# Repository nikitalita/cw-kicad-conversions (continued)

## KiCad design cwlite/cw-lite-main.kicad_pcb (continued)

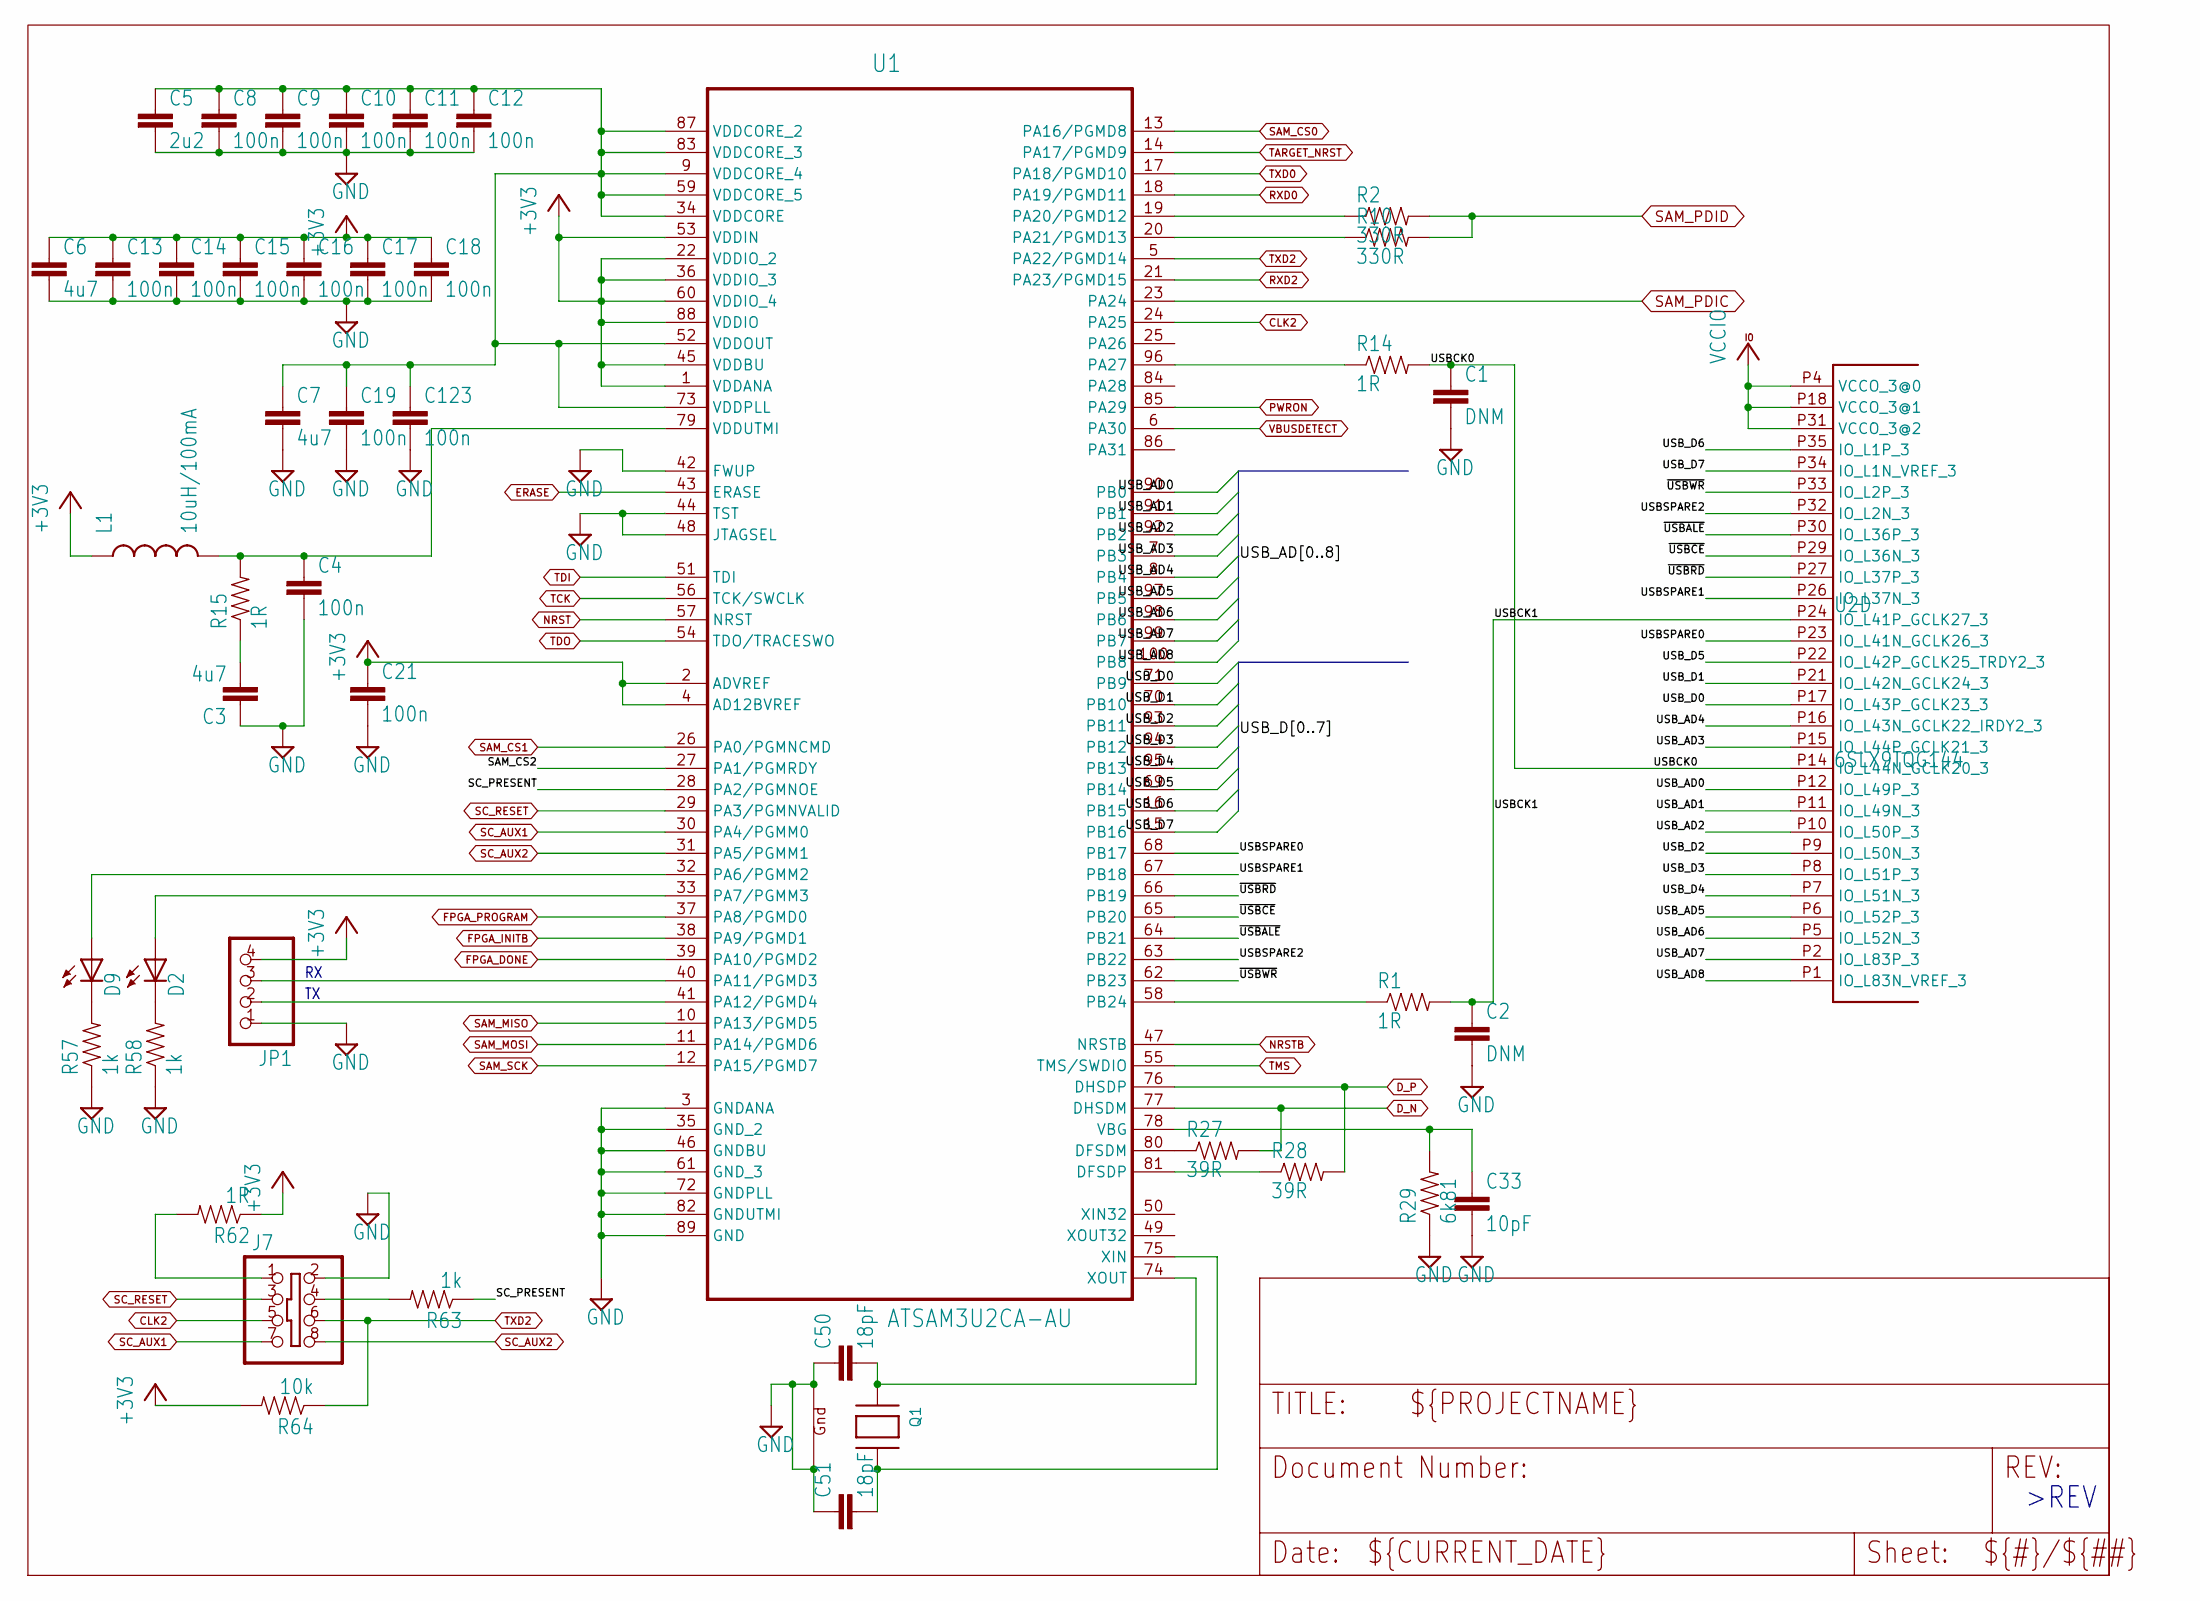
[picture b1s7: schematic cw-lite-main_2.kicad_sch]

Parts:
C1, C2: DNM; 0402C
C3, C6, C7: 4u7; 0603C
C4, C8, C9, C10, C11, C12, C13, C14, C15, C16, C17, C18, C19, C21, C123: 100n; 0402C
C5: 2u2; 0603C
C33: 10pF; 0603C
C50, C51: 18pF; 0402C
D2, D9: LED0603; LED-0603
J7: SHROUD_2X4EDGE; PINSHRD_EDGE_2X04.PAC
JP1: PINHD-1X4; 1X04
L1: 10uH/100mA; 0603
Q1: XTAL-4ABM8G; NX3225; MPN ABM8G-12.000MHZ-4Y-T3
R1, R14: 1R; 0402R
R2, R10: 330R; 0402R
R15, R62: 1R; 0603R
R27, R28: 39R; 0603R
R29: 6k81; 0402R
R57, R58, R63: 1k; 0603R
R64: 10k; 0603R
U1: ATSAM3U2CA-AU; QFP50P1600X1600X160-100N
U2: 6SLX9TQG144; TQ144; MPN XC6SLX9-3TQG144C

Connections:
+3V3: C6.1, C13.1, C14.1, C15.1, C16.1, C17.1, C18.1, C21.1, JP1.4, L1.1, R62.1, R64.2, U1.1 (VDDANA), U1.2 (ADVREF), U1.4 (AD12BVREF), U1.22 (VDDIO_2), U1.36 (VDDIO_3), U1.45 (VDDBU), U1.53 (VDDIN), U1.60 (VDDIO_4), U1.88 (VDDIO); also elsewhere on the board
/cw-lite-main_2/SAM_CS2: U1.27 (PA1/PGMRDY)
/cw-lite-main_2/SC_PRESENT: R63.1, U1.28 (PA2/PGMNOE)
/cw-lite-main_2/USBCK0: C1.1, R14.2, U2.P14 (IO_L44N_GCLK20_3)
/cw-lite-main_2/USBCK1: C2.1, R1.2, U2.P24 (IO_L41P_GCLK27_3)
/cw-lite-main_2/USBSPARE0: U1.68 (PB17), U2.P23 (IO_L41N_GCLK26_3)
/cw-lite-main_2/USBSPARE1: U1.67 (PB18), U2.P26 (IO_L37N_3)
/cw-lite-main_2/USBSPARE2: U1.63 (PB22), U2.P32 (IO_L2N_3)
/cw-lite-main_2/USB_AD0: U1.90 (PB0), U2.P12 (IO_L49P_3)
/cw-lite-main_2/USB_AD1: U1.91 (PB1), U2.P11 (IO_L49N_3)
/cw-lite-main_2/USB_AD2: U1.92 (PB2), U2.P10 (IO_L50P_3)
/cw-lite-main_2/USB_AD3: U1.7 (PB3), U2.P15 (IO_L44P_GCLK21_3)
/cw-lite-main_2/USB_AD4: U1.8 (PB4), U2.P16 (IO_L43N_GCLK22_IRDY2_3)
/cw-lite-main_2/USB_AD5: U1.97 (PB5), U2.P6 (IO_L52P_3)
/cw-lite-main_2/USB_AD6: U1.98 (PB6), U2.P5 (IO_L52N_3)
/cw-lite-main_2/USB_AD7: U1.99 (PB7), U2.P2 (IO_L83P_3)
/cw-lite-main_2/USB_AD8: U1.100 (PB8), U2.P1 (IO_L83N_VREF_3)
/cw-lite-main_2/USB_D0: U1.71 (PB9), U2.P17 (IO_L43P_GCLK23_3)
/cw-lite-main_2/USB_D1: U1.70 (PB10), U2.P21 (IO_L42N_GCLK24_3)
/cw-lite-main_2/USB_D2: U1.93 (PB11), U2.P9 (IO_L50N_3)
/cw-lite-main_2/USB_D3: U1.94 (PB12), U2.P8 (IO_L51P_3)
/cw-lite-main_2/USB_D4: U1.95 (PB13), U2.P7 (IO_L51N_3)
/cw-lite-main_2/USB_D5: U1.69 (PB14), U2.P22 (IO_L42P_GCLK25_TRDY2_3)
/cw-lite-main_2/USB_D6: U1.16 (PB15), U2.P35 (IO_L1P_3)
/cw-lite-main_2/USB_D7: U1.15 (PB16), U2.P34 (IO_L1N_VREF_3)
/cw-lite-main_2/~USBALE: U1.64 (PB21), U2.P30 (IO_L36P_3)
/cw-lite-main_2/~USBCE: U1.65 (PB20), U2.P29 (IO_L36N_3)
/cw-lite-main_2/~USBRD: U1.66 (PB19), U2.P27 (IO_L37P_3)
/cw-lite-main_2/~USBWR: U1.62 (PB23), U2.P33 (IO_L2P_3)
CLK2: J7.5, U1.24 (PA25); also elsewhere on the board
D_N: R27.2, U1.77 (DHSDM); also elsewhere on the board
D_P: R28.2, U1.76 (DHSDP); also elsewhere on the board
ERASE: U1.43 (ERASE); also elsewhere on the board
FPGA_DONE: U1.39 (PA10/PGMD2); also elsewhere on the board
FPGA_INITB: U1.38 (PA9/PGMD1); also elsewhere on the board
FPGA_PROGRAM: U1.37 (PA8/PGMD0); also elsewhere on the board
GND: C1.2, C2.2, C3.1, C4.2, C5.2, C6.2, C7.2, C8.2, C9.2, C10.2, C11.2, C12.2, C13.2, C14.2, C15.2, C16.2, C17.2, C18.2, C19.2, C21.2, C33.2, C50.1, C51.1, C123.2, J7.2, JP1.1, Q1.2 (G1), Q1.4 (G2), R29.1, R57.1, R58.1, U1.3 (GNDANA), U1.35 (GND_2), U1.42 (FWUP), U1.44 (TST), U1.46 (GNDBU), U1.48 (JTAGSEL), U1.61 (GND_3), U1.72 (GNDPLL), U1.82 (GNDUTMI), U1.89 (GND); also elsewhere on the board
NRST: U1.57 (NRST); also elsewhere on the board
NRSTB: U1.47 (NRSTB); also elsewhere on the board
unnamed: C3.2, R15.1
unnamed: D2.C, R58.2
unnamed: D9.C, R57.2
unnamed: J7.1, R62.2
unnamed: J7.4, R63.2
unnamed: C50.2, Q1.1 (X1), U1.74 (XOUT)
unnamed: C51.2, Q1.3 (X2), U1.75 (XIN)
unnamed: R27.1, U1.80 (DFSDM)
unnamed: R28.1, U1.81 (DFSDP)
unnamed: D9.A, U1.32 (PA6/PGMM2)
unnamed: D2.A, U1.33 (PA7/PGMM3)
unnamed: JP1.3, U1.40 (PA11/PGMD3)
unnamed: JP1.2, U1.41 (PA12/PGMD4)
unnamed: R2.1, U1.19 (PA20/PGMD12)
unnamed: R10.1, U1.20 (PA21/PGMD13)
unnamed: R14.1, U1.96 (PA27)
unnamed: R1.1, U1.58 (PB24)
unnamed: C33.1, R29.2, U1.78 (VBG)
unnamed: C5.1, C7.1, C8.1, C9.1, C10.1, C11.1, C12.1, C19.1, C123.1, U1.9 (VDDCORE_4), U1.34 (VDDCORE), U1.52 (VDDOUT), U1.59 (VDDCORE_5), U1.73 (VDDPLL), U1.83 (VDDCORE_3), U1.87 (VDDCORE_2)
unnamed: C4.1, L1.2, R15.2, U1.79 (VDDUTMI)
PWRON: U1.85 (PA29); also elsewhere on the board
RXD0: U1.18 (PA19/PGMD11); also elsewhere on the board
RXD2: U1.21 (PA23/PGMD15); also elsewhere on the board
SAM_CS0: U1.13 (PA16/PGMD8); also elsewhere on the board
SAM_CS1: U1.26 (PA0/PGMNCMD); also elsewhere on the board
SAM_MISO: U1.10 (PA13/PGMD5); also elsewhere on the board
SAM_MOSI: U1.11 (PA14/PGMD6); also elsewhere on the board
SAM_PDIC: U1.23 (PA24); also elsewhere on the board
SAM_PDID: R2.2, R10.2; also elsewhere on the board
SAM_SCK: U1.12 (PA15/PGMD7); also elsewhere on the board
SC_AUX1: J7.7, U1.30 (PA4/PGMM0); also elsewhere on the board
SC_AUX2: J7.8, U1.31 (PA5/PGMM1); also elsewhere on the board
SC_RESET: J7.3, U1.29 (PA3/PGMNVALID); also elsewhere on the board
TARGET_NRST: U1.14 (PA17/PGMD9); also elsewhere on the board
TCK: U1.56 (TCK/SWCLK); also elsewhere on the board
TDI: U1.51 (TDI); also elsewhere on the board
TDO: U1.54 (TDO/TRACESWO); also elsewhere on the board
TMS: U1.55 (TMS/SWDIO); also elsewhere on the board
TXD0: U1.17 (PA18/PGMD10); also elsewhere on the board
TXD2: J7.6, R64.1, U1.5 (PA22/PGMD14); also elsewhere on the board
VBUSDETECT: U1.6 (PA30); also elsewhere on the board
VCCIO: U2.P4 (VCCO_3@0), U2.P18 (VCCO_3@1), U2.P31 (VCCO_3@2); also elsewhere on the board

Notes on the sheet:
>REV

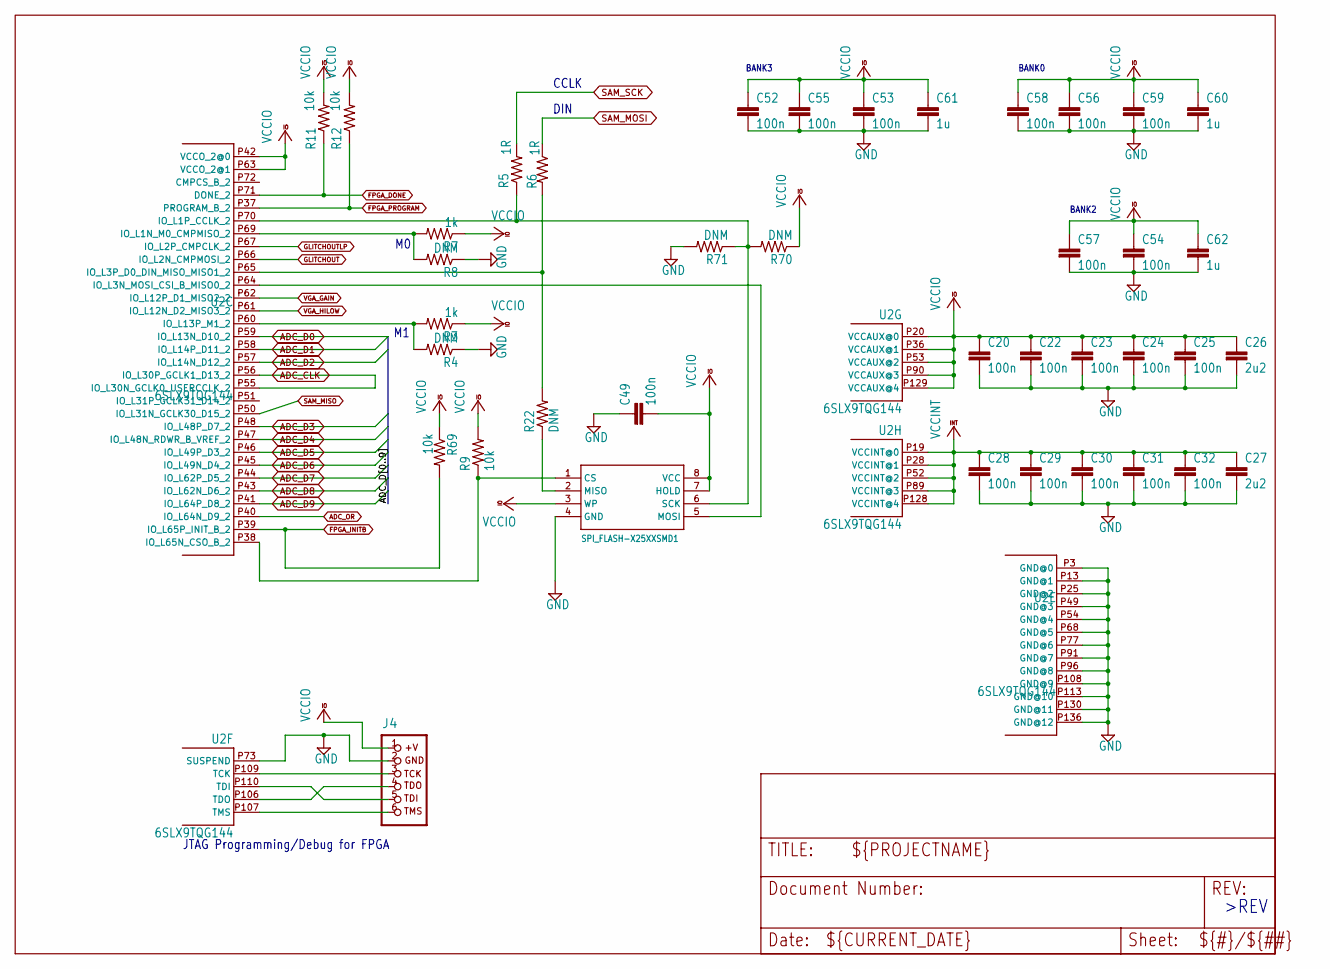
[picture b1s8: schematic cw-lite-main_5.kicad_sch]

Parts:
C20, C22, C23, C24, C25, C28, C29, C30, C31, C32, C52, C53, C54, C55, C56, C57, C58, C59: 100n; 0402C
C26, C27: 2u2; 0603C
C49: 100n; 0603C
C60, C61, C62: 1u; 0603C
J4: CON_HEADER_PRG_XILINX_JTAG6; HEADER_PRG_1X06
R3, R7: 1k; 0603R
R4, R8, R22: DNM; 0603R
R5, R6: 1R; 0402R
R9, R11, R12, R69: 10k; 0402R
R70, R71: DNM; 0402R
U2: 6SLX9TQG144; TQ144; MPN XC6SLX9-3TQG144C
U9: SPI_FLASH-X25XXSMD1; SO08-EIAJ

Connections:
ADC_CLK: U2.P55 (IO_L30N_GCLK0_USERCCLK_2), U2.P56 (IO_L30P_GCLK1_D13_2); also elsewhere on the board
ADC_D0: U2.P59 (IO_L13N_D10_2); also elsewhere on the board
ADC_D1: U2.P58 (IO_L14P_D11_2); also elsewhere on the board
ADC_D2: U2.P57 (IO_L14N_D12_2); also elsewhere on the board
ADC_D3: U2.P48 (IO_L48P_D7_2); also elsewhere on the board
ADC_D4: U2.P47 (IO_L48N_RDWR_B_VREF_2); also elsewhere on the board
ADC_D5: U2.P46 (IO_L49P_D3_2); also elsewhere on the board
ADC_D6: U2.P45 (IO_L49N_D4_2); also elsewhere on the board
ADC_D7: U2.P44 (IO_L62P_D5_2); also elsewhere on the board
ADC_D8: U2.P43 (IO_L62N_D6_2); also elsewhere on the board
ADC_D9: U2.P41 (IO_L64P_D8_2); also elsewhere on the board
ADC_OR: U2.P40 (IO_L64N_D9_2); also elsewhere on the board
FPGA_DONE: R11.1, U2.P71 (DONE_2); also elsewhere on the board
FPGA_INITB: R69.2, U2.P39 (IO_L65P_INIT_B_2); also elsewhere on the board
FPGA_PROGRAM: R12.1, U2.P37 (PROGRAM_B_2); also elsewhere on the board
GLITCHOUT: U2.P66 (IO_L2N_CMPMOSI_2); also elsewhere on the board
GLITCHOUTLP: U2.P67 (IO_L2P_CMPCLK_2); also elsewhere on the board
GND: C20.2, C22.2, C23.2, C24.2, C25.2, C26.2, C27.2, C28.2, C29.2, C30.2, C31.2, C32.2, C49.1, C52.2, C53.2, C54.2, C55.2, C56.2, C57.2, C58.2, C59.2, C60.2, C61.2, C62.2, J4.2 (GND), R4.1, R8.1, R71.2, U2.P3 (GND@0), U2.P13 (GND@1), U2.P25 (GND@2), U2.P49 (GND@3), U2.P54 (GND@4), U2.P68 (GND@5), U2.P73 (SUSPEND), U2.P77 (GND@6), U2.P91 (GND@7), U2.P96 (GND@8), U2.P108 (GND@9), U2.P113 (GND@10), U2.P130 (GND@11), U2.P136 (GND@12), U9.4 (GND); also elsewhere on the board
unnamed: J4.3 (TCK), U2.P109 (TCK)
unnamed: J4.5 (TDI), U2.P110 (TDI)
unnamed: J4.4 (TDO), U2.P106 (TDO)
unnamed: J4.6 (TMS), U2.P107 (TMS)
unnamed: R7.2, R8.2, U2.P69 (IO_L1N_M0_CMPMISO_2)
unnamed: R5.1, R70.2, R71.1, U2.P70 (IO_L1P_CCLK_2), U9.6 (SCK)
unnamed: U2.P64 (IO_L3N_MOSI_CSI_B_MISO0_2), U9.5 (MOSI)
unnamed: R6.2, R22.2, U2.P65 (IO_L3P_D0_DIN_MISO_MISO1_2)
unnamed: R3.2, R4.2, U2.P60 (IO_L13P_M1_2)
unnamed: R9.1, U2.P38 (IO_L65N_CSO_B_2), U9.1 (CS)
unnamed: R22.1, U9.2 (MISO)
SAM_MISO: U2.P50 (IO_L31N_GCLK30_D15_2); also elsewhere on the board
SAM_MOSI: R6.1; also elsewhere on the board
SAM_SCK: R5.2; also elsewhere on the board
VCCINT: C27.1, C28.1, C29.1, C30.1, C31.1, C32.1, U2.P19 (VCCINT@0), U2.P28 (VCCINT@1), U2.P52 (VCCINT@2), U2.P89 (VCCINT@3), U2.P128 (VCCINT@4); also elsewhere on the board
VCCIO: C20.1, C22.1, C23.1, C24.1, C25.1, C26.1, C49.2, C52.1, C53.1, C54.1, C55.1, C56.1, C57.1, C58.1, C59.1, C60.1, C61.1, C62.1, J4.1 (+V), R3.1, R7.1, R9.2, R11.2, R12.2, R69.1, R70.1, U2.P20 (VCCAUX@0), U2.P36 (VCCAUX@1), U2.P42 (VCCO_2@0), U2.P53 (VCCAUX@2), U2.P63 (VCCO_2@1), U2.P90 (VCCAUX@3), U2.P129 (VCCAUX@4), U9.3 (WP), U9.7 (HOLD), U9.8 (VCC); also elsewhere on the board
VGA_GAIN: U2.P62 (IO_L12P_D1_MISO2_2); also elsewhere on the board
VGA_HILOW: U2.P61 (IO_L12N_D2_MISO3_2); also elsewhere on the board

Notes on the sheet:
>REV
JTAG Programming/Debug for FPGA
BANK3
BANK2
DIN
BANK0
CCLK

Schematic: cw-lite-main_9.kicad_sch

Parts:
C37: 47u; 0805
C103: 10u; 0603C
C104: 10n; 0603C
C105, C107: 1u; 0603C
C106, C108, C109: 100n; 0603C
C115, C116, C121: DNM; 0603C
C118, C119, C120: CAP0603-CAP; 0603C
J2: SHROUD_2X10-SHROUDED; PINSHRD_PTH_2X10
J9: MICRO-USB-5P-ZX62D-B-5P8; B-SMD-5P-TH
JP6, JP7, JP12: PINHD-1X2; 1X02
JP13: PINHD-1X9; 1X09-BIG
JP14, JP15, JP16, JP17: PINHD-1X1; 1X01
L10: 1k/500mA; FB603
LED9, LED10: LED-0603; LED-603
Q2: CRYSTALHC49U-V; HC49U-V
R13: 10k; 0603R
R66, R76: 49R9; 0805
R67, R72: 100R; 0603R
R73: DNM; 0603R
R74, R75: 1k; 0603R
SJ2: SOLDERJUMPER_2WAYPASTE2&3; SJ_3_PASTE2&3
SJ3, SJ4, SJ5, SJ7: SOLDERJUMPERNC; SJ_2S
U11: V_REG_MIC2920; SOT223
U12: XMEGA16A4A; TQFP44; MPN ATXMEGA128A4U-AU
X3, X5: SMA-NOSILK; J502-ND-142-0711-821_826-NOSILK

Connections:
/cw-lite-main_9/TPC6: JP13.8, U12.16 (PC6)
/cw-lite-main_9/TPC7: JP13.7, U12.17 (PC7)
/cw-lite-main_9/TUSB_N: J9.2 (DM), U12.26 (PD6)
/cw-lite-main_9/TUSB_P: J9.3 (DP), U12.27 (PD7)
/cw-lite-main_9/VCC_TARG: C103.1, C104.1, L10.1, R13.1, R74.2, R75.2, SJ2.2, SJ7.1
ANIN: JP7.2, SJ4.2, X3.1; also elsewhere on the board
GND: C37.2, C103.2, C104.2, C105.2, C106.2, C107.2, C108.2, C109.1, C115.2, C116.1, C118.1, C119.1, C120.1, C121.1, J2.2, J2.17, J2.19, J9.5 (GND@1), JP13.9, U11.2 (GND), U12.8 (GND), U12.18 (GND1), U12.30 (GND2), U12.38 (GND3), X3.G@1 (2), X3.G@2 (2), X3.G@3 (2), X3.G@4 (2), X5.G@1 (2), X5.G@2 (2), X5.G@3 (2), X5.G@4 (2); also elsewhere on the board
unnamed: C37.1, C105.1, C106.1, JP12.2, R76.1, SJ3.1
unnamed: C118.2, J9.E1 (SHIELD), J9.E2 (SHIELD), J9.P$1 (SHIELD), J9.P$2 (SHIELD), J9.P$3 (SHIELD), J9.P$4 (SHIELD)
unnamed: C119.2, J9.1 (VCC), U11.1 (IN)
unnamed: L10.2, R76.2
unnamed: LED9.A, R74.1
unnamed: LED10.A, R75.1
unnamed: C120.2, SJ2.1, U11.3 (OUT)
unnamed: C107.1, C108.1, C109.2, JP12.1, R66.2, SJ3.2, U12.39 (AVCC)
unnamed: LED9.C, U12.1 (PA5)
unnamed: LED10.C, U12.2 (PA6)
unnamed: R67.2, U12.7 (PB3)
unnamed: JP13.6, U12.20 (PD0)
unnamed: JP13.5, U12.21 (PD1)
unnamed: JP13.4, U12.22 (PD2)
unnamed: JP13.3, U12.23 (PD3)
unnamed: JP13.2, U12.24 (PD4)
unnamed: JP13.1, U12.25 (PD5)
unnamed: C116.2, Q2.1, R73.1, U12.36 (PR0(XT2))
unnamed: C115.1, Q2.2, R72.1, U12.37 (PR1(XT1))
unnamed: C121.2, JP6.1, JP7.1, R66.1, SJ4.1, SJ5.1, U12.9 (VCC), U12.19 (VCC1), U12.31 (VCC2)
THS1: J2.4, R67.1; also elsewhere on the board
THS2: J2.6, R72.2, R73.2; also elsewhere on the board
TIO1: J2.10, JP16.1, U12.13 (PC3); also elsewhere on the board
TIO2: J2.12, JP17.1, U12.12 (PC2); also elsewhere on the board
TIO3: J2.14, JP14.1, U12.41 (PA1); also elsewhere on the board
TIO4: J2.16, JP15.1, U12.40 (PA0); also elsewhere on the board
TMISO: J2.7; also elsewhere on the board
TMOSI: J2.9; also elsewhere on the board
TPDIC: J2.13, R13.2, U12.35 (~RESET/PDI_CLK); also elsewhere on the board
TPDID: J2.15, U12.34 (PDI_DATA); also elsewhere on the board
TRST: J2.5; also elsewhere on the board
TSCK: J2.11; also elsewhere on the board
TVREF: J2.8; also elsewhere on the board
VCCGLITCH: JP6.2, SJ5.2, X5.1; also elsewhere on the board
VCCTIO_SWITCHED: J2.3, J2.18, SJ2.3; also elsewhere on the board

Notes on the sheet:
>REV
Breakaway Section of PCB
Might be XMEGA128D3 instead?

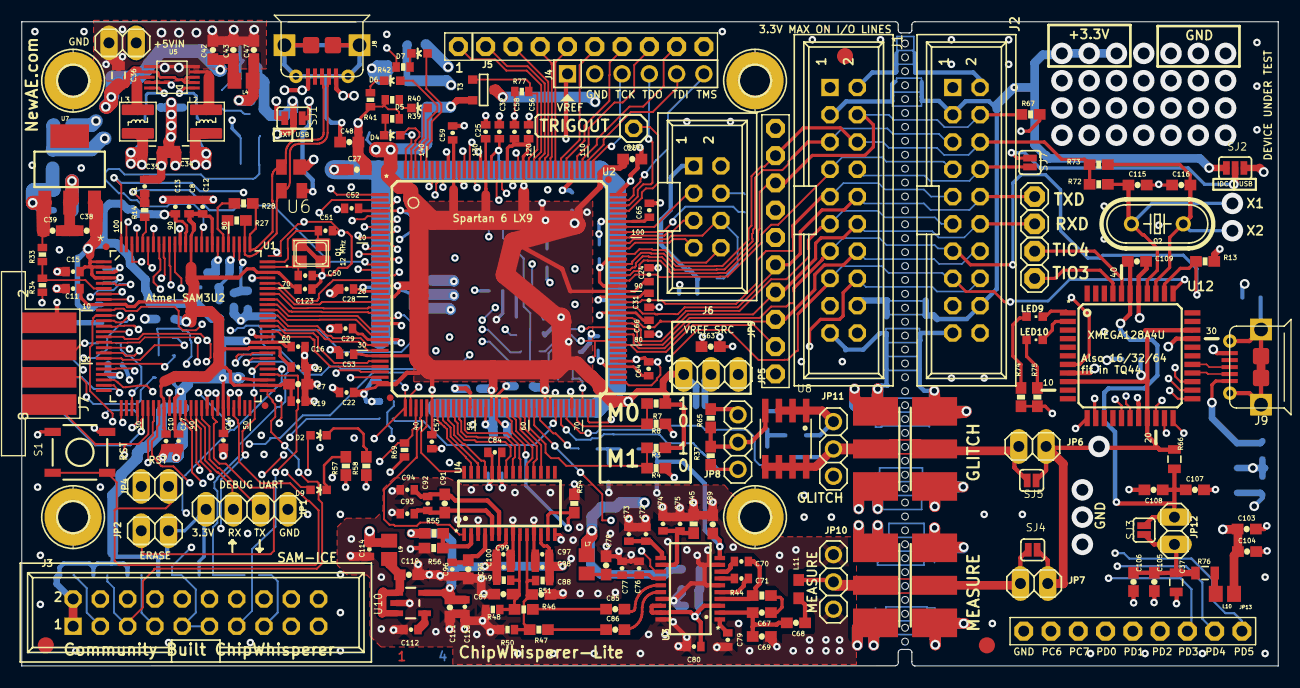
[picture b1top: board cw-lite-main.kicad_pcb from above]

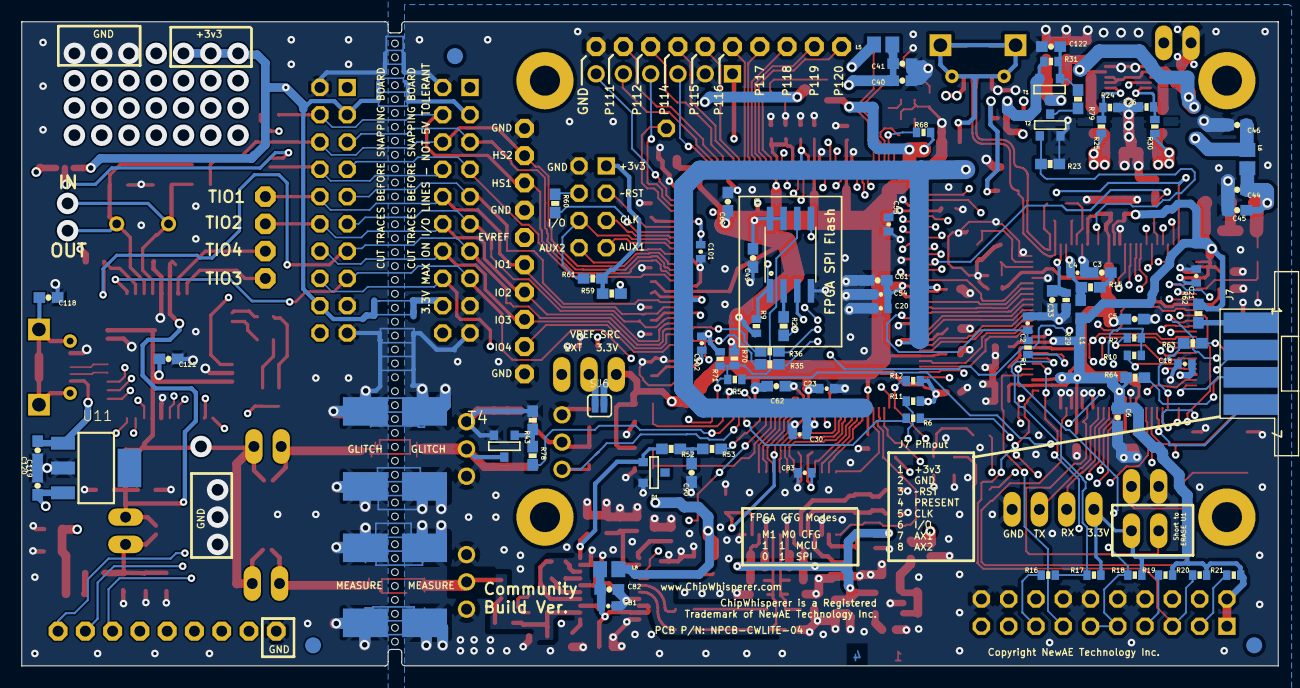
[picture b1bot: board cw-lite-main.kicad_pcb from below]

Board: 4 copper layers, 117.0 x 60.0 mm, 334 parts (86 on the bottom side), 223 nets.

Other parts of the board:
@HOLE0, @HOLE1, @HOLE2, @HOLE3, @HOLE4, @HOLE5, @HOLE6, @HOLE7, @HOLE8, @HOLE9, @HOLE10, @HOLE11, @HOLE12, @HOLE13, @HOLE14, @HOLE15, @HOLE16, @HOLE17, @HOLE18, @HOLE19, @HOLE20, @HOLE21, @HOLE22, @HOLE23, @HOLE24, @HOLE25, @HOLE26, @HOLE27, @HOLE28, @HOLE29, @HOLE30, @HOLE31, @HOLE32, @HOLE33, @HOLE34, @HOLE35, @HOLE36, @HOLE37, @HOLE38, @HOLE39, @HOLE40, @HOLE41, @HOLE42, @HOLE43: (no value)

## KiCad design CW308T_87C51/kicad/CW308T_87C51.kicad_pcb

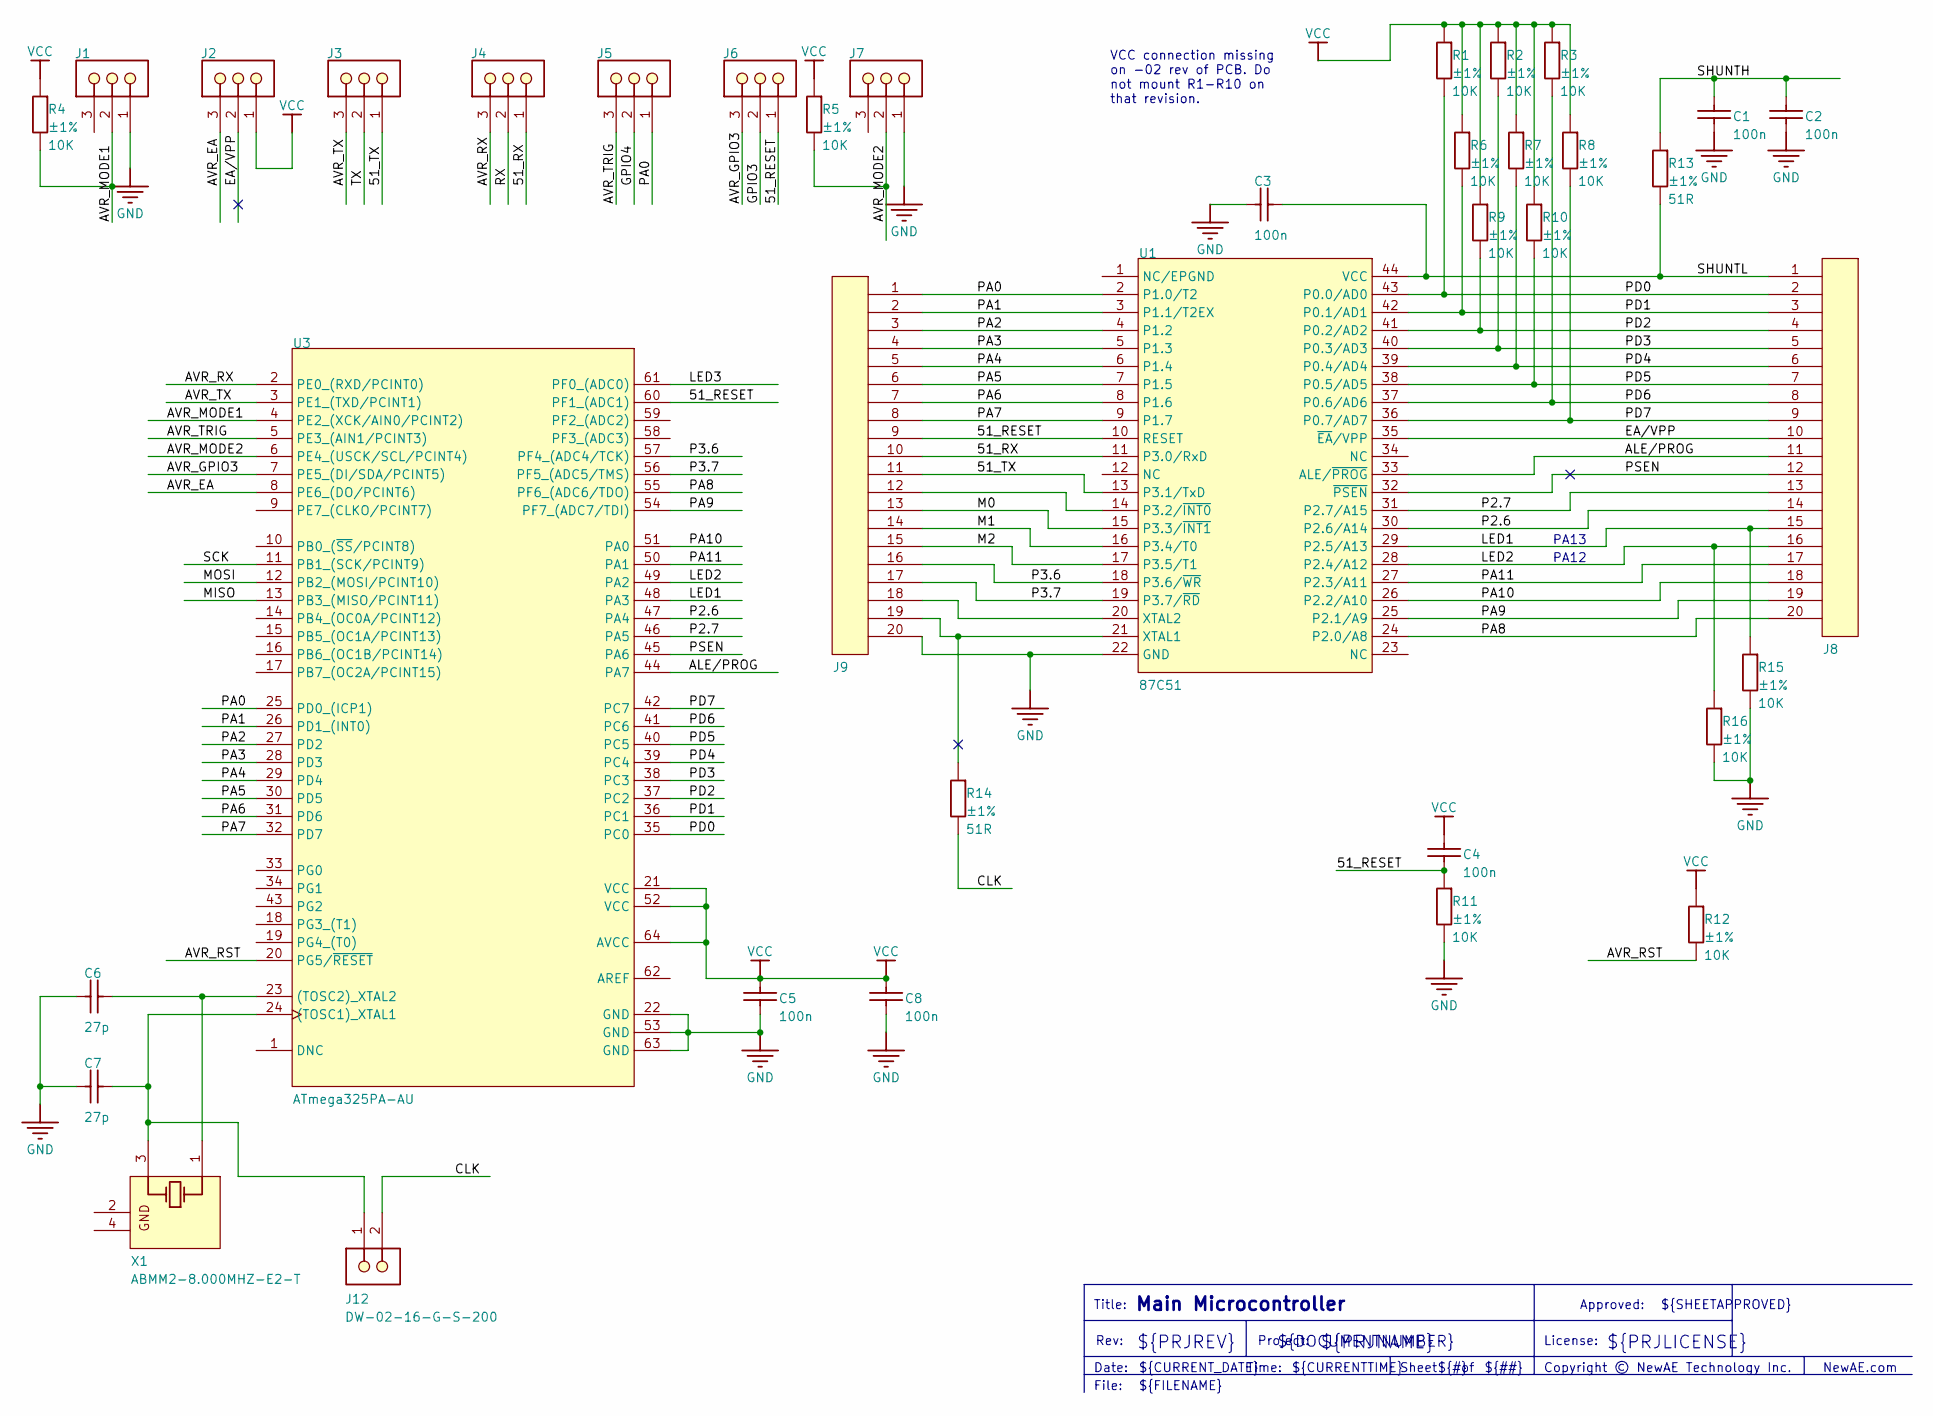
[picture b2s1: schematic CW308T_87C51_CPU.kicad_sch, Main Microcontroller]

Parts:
C1, C2, C3, C5, C8: 100nf; CAPC1608X90N; TOLERANCE ±10%; RATINGS 50V; X7R; MANUFACTURER PART NUMBE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 C1608X7R1H104K
C4: 100n; CAPC1608X90N; TOLERANCE ±10%; RATINGS 50V; X7R; MANUFACTURER PART NUMBE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 C1608X7R1H104K
C6, C7: 27p; CAPC1608X90N; TOLERANCE ±1%; RATINGS 100V; NP0; MANUFACTURER PART NUMBE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 06031A270FAT2A
J1, J2, J3, J4, J5, J6, J7: 68000-203HLF; SMTC-TSW-103-07-X-S; PARTNUMBER 68000-203HLF
J8, J9: 20-Pin Header; 801-87-020-10-001101; MANUFACTURE PART NUMBER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 801-87-020-10-001101
J12: DW-02-16-G-S-200; SMTC-DW-02-16-X-S-200; PARTNUMBER DW-02-16-G-S-200
R1, R2, R3, R4, R5, R6, R7, R8, R9, R10, R11, R12, R15, R16: 10K; RESC1608X55N; RATINGS 1/10W; TOLERANCE ±1%; MANUFACTURER PART NUMBE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 RC0603FR-0710KL
R13, R14: 51R; RESC1608X55N; RATINGS 1/10 W; TOLERANCE ±1%; MANUFACTURER PART NUMBE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 RC0603FR-0751RL
U1: 87C51; PLCC44_SOCKET
U3: ATmega325PA-AU; 64A_M
X1: ABMM2-8.000MHZ-E2-T; ABRA-ABMM2-4_V; PARTNUMBER ABMM2-8.000MHZ-E2-T

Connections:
/CPU/51_RESET: C4.2, J6.1, J9.9, R11.1, U1.10 (RESET), U3.60 (PF1_(ADC1))
/CPU/51_RX: J4.1, J9.10, U1.11 (P3.0/RxD)
/CPU/51_TX: J3.1, J9.11, U1.13 (P3.1/TxD)
/CPU/ALE/PROG: J8.11, U1.33 (ALE/~PROG), U3.44 (PA7)
/CPU/AVR_EA: J2.3, U3.8 (PE6_(DO/PCINT6))
/CPU/AVR_GPIO3: J6.3, U3.7 (PE5_(DI/SDA/PCINT5))
/CPU/AVR_MODE1: J1.2, R4.2, U3.4 (PE2_(XCK/AIN0/PCINT2))
/CPU/AVR_MODE2: J7.2, R5.1, U3.6 (PE4_(USCK/SCL/PCINT4))
/CPU/AVR_RST: R12.2, U3.20 (PG5/~RESET)
/CPU/AVR_RX: J4.3, U3.2 (PE0_(RXD/PCINT0))
/CPU/AVR_TRIG: J5.3, U3.5 (PE3_(AIN1/PCINT3))
/CPU/AVR_TX: J3.3, U3.3 (PE1_(TXD/PCINT1))
/CPU/CLK: J12.2, R14.2
/CPU/EA/VPP: J2.2, J8.10, U1.35 (~EA/VPP)
/CPU/GPIO3: J6.2
/CPU/GPIO4: J5.2
/CPU/LED1: J8.15, R15.1, U1.29 (P2.5/A13), U3.48 (PA3)
/CPU/LED2: J8.16, R16.1, U1.28 (P2.4/A12), U3.49 (PA2)
/CPU/LED3: U3.61 (PF0_(ADC0))
/CPU/M0: J9.13, U1.15 (P3.3/~INT1)
/CPU/M1: J9.14, U1.16 (P3.4/T0)
/CPU/M2: J9.15, U1.17 (P3.5/T1)
/CPU/MISO: U3.13 (PB3_(MISO/PCINT11))
/CPU/MOSI: U3.12 (PB2_(MOSI/PCINT10))
/CPU/P2.6: J8.14, U1.30 (P2.6/A14), U3.47 (PA4)
/CPU/P2.7: J8.13, U1.31 (P2.7/A15), U3.46 (PA5)
/CPU/P3.6: J9.16, U1.18 (P3.6/~WR), U3.57 (PF4_(ADC4/TCK))
/CPU/P3.7: J9.17, U1.19 (P3.7/~RD), U3.56 (PF5_(ADC5/TMS))
/CPU/PA0: J5.1, J9.1, U1.2 (P1.0/T2), U3.25 (PD0_(ICP1))
/CPU/PA1: J9.2, U1.3 (P1.1/T2EX), U3.26 (PD1_(INT0))
/CPU/PA2: J9.3, U1.4 (P1.2), U3.27 (PD2)
/CPU/PA3: J9.4, U1.5 (P1.3), U3.28 (PD3)
/CPU/PA4: J9.5, U1.6 (P1.4), U3.29 (PD4)
/CPU/PA5: J9.6, U1.7 (P1.5), U3.30 (PD5)
/CPU/PA6: J9.7, U1.8 (P1.6), U3.31 (PD6)
/CPU/PA7: J9.8, U1.9 (P1.7), U3.32 (PD7)
/CPU/PA8: J8.20, U1.24 (P2.0/A8), U3.55 (PF6_(ADC6/TDO))
/CPU/PA9: J8.19, U1.25 (P2.1/A9), U3.54 (PF7_(ADC7/TDI))
/CPU/PA10: J8.18, U1.26 (P2.2/A10), U3.51 (PA0)
/CPU/PA11: J8.17, U1.27 (P2.3/A11), U3.50 (PA1)
/CPU/PD0: J8.2, R1.2, U1.43 (P0.0/AD0), U3.35 (PC0)
/CPU/PD1: J8.3, R6.2, U1.42 (P0.1/AD1), U3.36 (PC1)
/CPU/PD2: J8.4, R9.2, U1.41 (P0.2/AD2), U3.37 (PC2)
/CPU/PD3: J8.5, R2.2, U1.40 (P0.3/AD3), U3.38 (PC3)
/CPU/PD4: J8.6, R7.2, U1.39 (P0.4/AD4), U3.39 (PC4)
/CPU/PD5: J8.7, R10.2, U1.38 (P0.5/AD5), U3.40 (PC5)
/CPU/PD6: J8.8, R3.2, U1.37 (P0.6/AD6), U3.41 (PC6)
/CPU/PD7: J8.9, R8.2, U1.36 (P0.7/AD7), U3.42 (PC7)
/CPU/PSEN: J8.12, U1.32 (~PSEN), U3.45 (PA6)
/CPU/RX: J4.2
/CPU/SCK: U3.11 (PB1_(SCK/PCINT9))
/CPU/SHUNTH: C1.1, C2.1, R13.1
/CPU/SHUNTL: C3.2, J8.1, R13.2, U1.44 (VCC)
/CPU/TX: J3.2
GND: C1.2, C2.2, C3.1, C5.2, C6.1, C7.1, C8.2, J1.1, J7.1, J9.20, R11.2, R15.2, R16.2, U1.22 (GND), U3.22 (GND), U3.53 (GND), U3.63 (GND); also elsewhere on the board
unnamed: J9.12, U1.14 (P3.2/~INT0)
unnamed: J9.19, R14.1, U1.21 (XTAL1)
unnamed: J9.18, U1.20 (XTAL2)
unnamed: C7.2, J12.1, U3.24 ((TOSC1)_XTAL1), X1.3 (X2)
unnamed: C6.2, U3.23 ((TOSC2)_XTAL2), X1.1 (X1)
VCC: C4.1, C5.1, C8.1, J2.1, R1.1, R2.1, R3.1, R4.1, R5.2, R6.1, R7.1, R8.1, R9.1, R10.1, R12.1, U3.21 (VCC), U3.52 (VCC), U3.64 (AVCC); also elsewhere on the board

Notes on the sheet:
VCC connection missing on -02 rev of PCB. Do not mount R1-R10 on that revision.
${FILENAME}
${##}
Title:
License:
${TITLE}
Approved:
${CURRENT_DATE}
NewAE.com
${PRJNAME}
Date:
Sheet
Rev:
Time:
${SHEETAPPROVED}
${PRJLICENSE}
Copyright © NewAE Technology Inc.
${REVISION}
Project:
File:
${PRJREV}
PA12
${CURRENTTIME}
${#}
${DOCUMENTNUMBER}
PA13

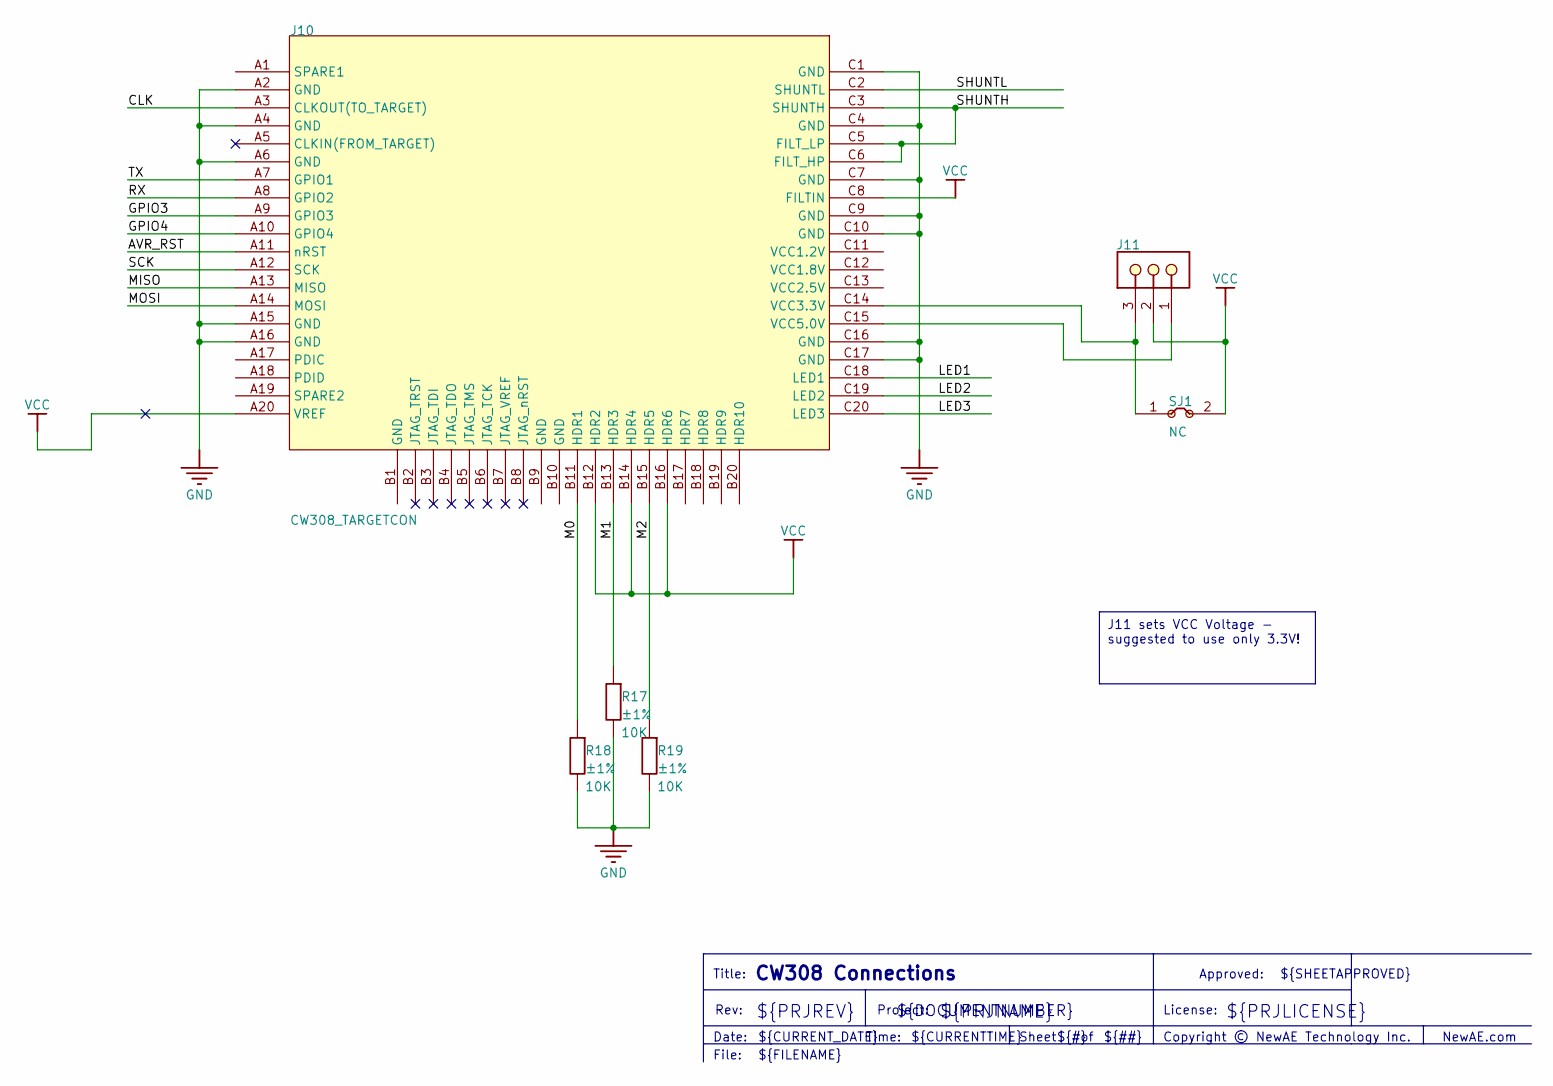
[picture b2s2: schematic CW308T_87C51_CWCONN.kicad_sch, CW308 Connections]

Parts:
J10: CW308_TARGETCON; CW308_TBOARD_CONN
J11: 68000-203HLF; SMTC-TSW-103-07-X-S; PARTNUMBER 68000-203HLF
R17, R18, R19: 10K; RESC1608X55N; RATINGS 1/10W; TOLERANCE ±1%; MANUFACTURER PART NUMBE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 RC0603FR-0710KL
SJ1: NC; SJ_2S_NC; PART NUMBER SJ_2S

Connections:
/CWCONN/AVR_RST: J10.A11 (nRST)
/CWCONN/CLK: J10.A3 (CLKOUT(TO_TARGET))
/CWCONN/GPIO3: J10.A9 (GPIO3)
/CWCONN/GPIO4: J10.A10 (GPIO4)
/CWCONN/LED1: J10.C18 (LED1)
/CWCONN/LED2: J10.C19 (LED2)
/CWCONN/LED3: J10.C20 (LED3)
/CWCONN/M0: J10.B11 (HDR1), R18.1
/CWCONN/M1: J10.B13 (HDR3), R17.1
/CWCONN/M2: J10.B15 (HDR5), R19.2
/CWCONN/MISO: J10.A13 (MISO)
/CWCONN/MOSI: J10.A14 (MOSI)
/CWCONN/RX: J10.A8 (GPIO2)
/CWCONN/SCK: J10.A12 (SCK)
/CWCONN/SHUNTH: J10.C3 (SHUNTH), J10.C5 (FILT_LP), J10.C6 (FILT_HP)
/CWCONN/SHUNTL: J10.C2 (SHUNTL)
/CWCONN/TX: J10.A7 (GPIO1)
GND: J10.A2 (GND), J10.A4 (GND), J10.A6 (GND), J10.A15 (GND), J10.A16 (GND), J10.C1 (GND), J10.C4 (GND), J10.C7 (GND), J10.C9 (GND), J10.C10 (GND), J10.C16 (GND), J10.C17 (GND), R17.2, R18.2, R19.1; also elsewhere on the board
unnamed: J10.C14 (VCC3.3V), J11.3, SJ1.1
unnamed: J10.C15 (VCC5.0V), J11.1
VCC: J10.A20 (VREF), J10.B12 (HDR2), J10.B14 (HDR4), J10.B16 (HDR6), J10.C8 (FILTIN), J11.2, SJ1.2; also elsewhere on the board

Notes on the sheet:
J11 sets VCC Voltage - suggested to use only 3.3V!
Rev:
${PRJNAME}
${FILENAME}
${CURRENT_DATE}
Title:
${SHEETAPPROVED}
${DOCUMENTNUMBER}
Sheet
Date:
${PRJREV}
${##}
${#}
Approved:
File:
NewAE.com
Project:
${CURRENTTIME}
${PRJLICENSE}
License:
Time:
${REVISION}
Copyright © NewAE Technology Inc.
${TITLE}
